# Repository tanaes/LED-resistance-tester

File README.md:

# LED-resistance-tester
Simple PCB for dialing in current limiting resistors for LEDs

## Inspiration

This project was broadly inspired by [this blog post on Sparkfun](https://news.sparkfun.com/5461), combined of course with the unceasing voice in my head to *design another stupid PCB*. 

## Usage

I set this board up to have four LED test 'stations' each on two parallel power rails. The idea is that you can easily match your brightness on, say, 5V and 24V. There's a jumper to link the two rails, too, in case you just want to test 8 different LEDs at the same voltage. There are big, ø5mm plated holes that are just the right size for grabbing with alligator clips for powering, as well as 5mm terminal blocks. 

LED current is set with DIP switches jumping over a ~ decadal series of common resistor values, with a minimum series resistance of 220Ω and a maximum of about 41kΩ (because DIP switches are fun).

Solder jumpers in parallel to the DIP switches offer an alternative (archival) mechanism, on the theory that one might want to dial this in for a particular vendor series and then toss it in a drawer for future reference. 

There are footprints for 0603 and 0805 SMT plus THT LEDs per channel, as well as big test pads for double-checking resistance values. 

Big white silkscreen areas are present on the front and back, in principle as a place to write down what the heck you have soldered onto the board for when you come across it in that drawer a year from now.

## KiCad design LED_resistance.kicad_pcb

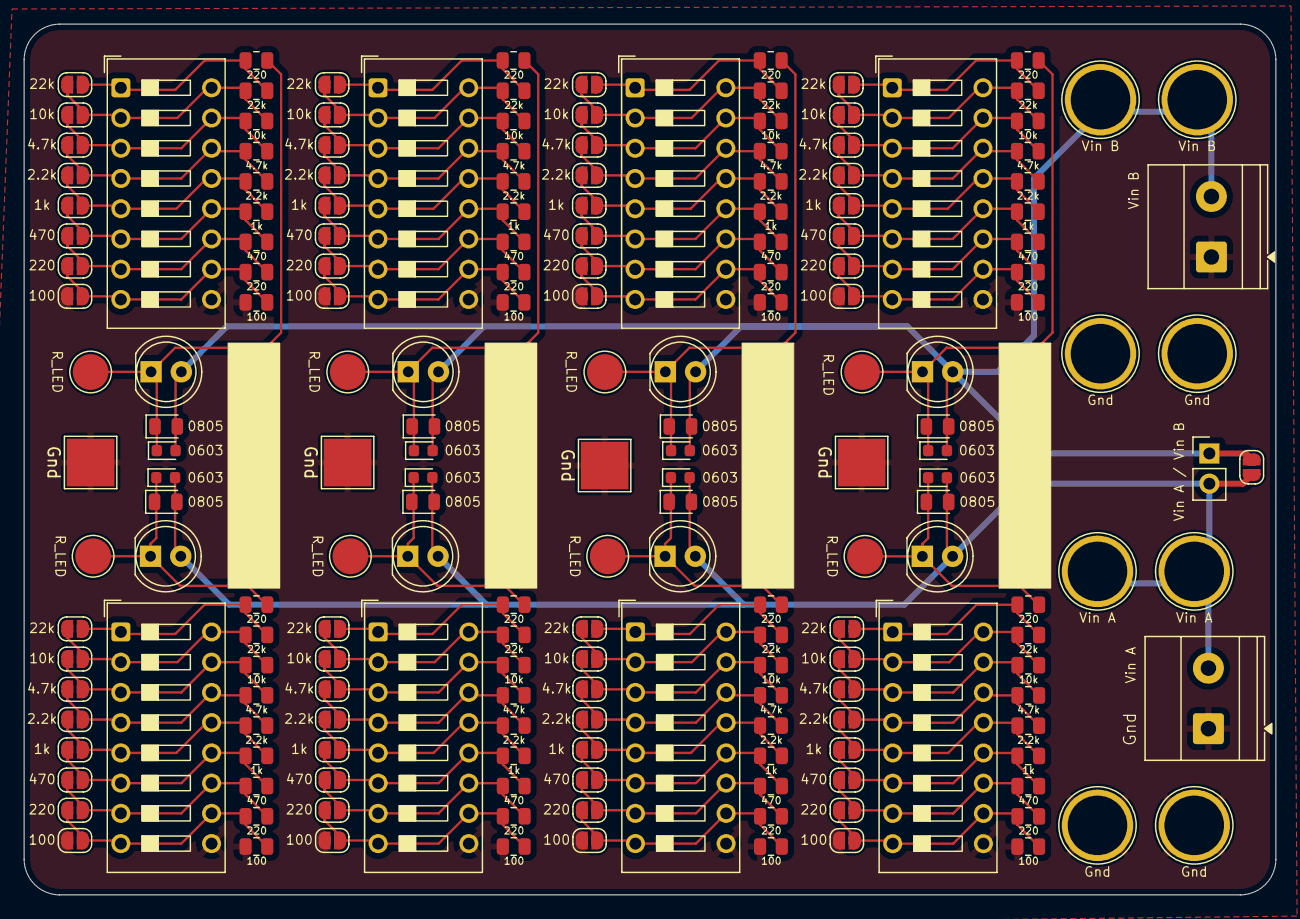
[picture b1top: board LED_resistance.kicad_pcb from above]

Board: 2 copper layers, 105.2 x 73.2 mm, 192 parts (0 on the bottom side), 75 nets.

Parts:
D1, D4, D7, D10, D13, D16, D19, D22: THT; LED_D5.0mm
D2, D5, D8, D11, D14, D17, D20, D23: 0805; LED_0805_2012Metric
D3, D6, D9, D12, D15, D18, D21, D24: 0603; LED_0603_1608Metric
J1: Vin A; TerminalBlock_Phoenix_MKDS-1,5-2-5.08_1x02_P5.08mm_Horizont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
J2: Vin B; TerminalBlock_Phoenix_MKDS-1,5-2-5.08_1x02_P5.08mm_Horizont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
JP1, JP9, JP17, JP25, JP33, JP41, JP49, JP57: 22k; SolderJumper-2_P1.3mm_Open_RoundedPad1.0x1.5mm
JP2, JP10, JP18, JP26, JP34, JP42, JP50, JP58: 10k; SolderJumper-2_P1.3mm_Open_RoundedPad1.0x1.5mm
JP3, JP11, JP19, JP27, JP35, JP43, JP51, JP59: 4.7k; SolderJumper-2_P1.3mm_Open_RoundedPad1.0x1.5mm
JP4, JP12, JP20, JP28, JP36, JP44, JP52, JP60: 2.2k; SolderJumper-2_P1.3mm_Open_RoundedPad1.0x1.5mm
JP5, JP13, JP21, JP29, JP37, JP45, JP53, JP61: 1k; SolderJumper-2_P1.3mm_Open_RoundedPad1.0x1.5mm
JP6, JP14, JP22, JP30, JP38, JP46, JP54, JP62: 470; SolderJumper-2_P1.3mm_Open_RoundedPad1.0x1.5mm
JP7, JP15, JP23, JP31, JP39, JP47, JP55, JP63: 220; SolderJumper-2_P1.3mm_Open_RoundedPad1.0x1.5mm
JP8, JP16, JP24, JP32, JP40, JP48, JP56, JP64: 100; SolderJumper-2_P1.3mm_Open_RoundedPad1.0x1.5mm
JP65: SolderJumper_2_Open; SolderJumper-2_P1.3mm_Open_RoundedPad1.0x1.5mm
JP66: Vin A / Vin B; PinHeader_1x02_P2.54mm_Vertical
R1, R8, R10, R17, R19, R26, R28, R35, R37, R44, R46, R53, R55, R62, R64, R71: 220; R_0805_2012Metric
R2, R11, R20, R29, R38, R47, R56, R65: 22k; R_0805_2012Metric
R3, R12, R21, R30, R39, R48, R57, R66: 10k; R_0805_2012Metric
R4, R13, R22, R31, R40, R49, R58, R67: 4.7k; R_0805_2012Metric
R5, R14, R23, R32, R41, R50, R59, R68: 2.2k; R_0805_2012Metric
R6, R15, R24, R33, R42, R51, R60, R69: 1k; R_0805_2012Metric
R7, R16, R25, R34, R43, R52, R61, R70: 470; R_0805_2012Metric
R9, R18, R27, R36, R45, R54, R63, R72: 100; R_0805_2012Metric
SW1, SW2, SW3, SW4, SW5, SW6, SW7, SW8: SW_DIP_x08; SW_DIP_SPSTx08_Slide_9.78x22.5mm_W7.62mm_P2.54mm
TP1, TP3: Vin A; TestPoint_Plated_Hole_D5.0mm
TP2, TP4, TP10, TP12: Gnd; TestPoint_Plated_Hole_D5.0mm
TP5, TP6, TP7, TP8, TP13, TP14, TP15, TP16: R_LED; TestPoint_Pad_D3.0mm
TP9, TP11: Vin B; TestPoint_Plated_Hole_D5.0mm
TP17, TP18, TP19, TP20: Gnd; TestPoint_Pad_4.0x4.0mm

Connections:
/led_subset2/Vin: D13.2 (A), D14.2 (A), D15.2 (A), D16.2 (A), D17.2 (A), D18.2 (A), D19.2 (A), D20.2 (A), D21.2 (A), D22.2 (A), D23.2 (A), D24.2 (A), J2.2, JP65.1 (A), JP66.1 (A), TP9.1, TP11.1
/led_subset/Vin: D1.2 (A), D2.2 (A), D3.2 (A), D4.2 (A), D5.2 (A), D6.2 (A), D7.2 (A), D8.2 (A), D9.2 (A), D10.2 (A), D11.2 (A), D12.2 (A), J1.2, JP65.2 (B), JP66.2 (B), TP1.1, TP3.1
GND: J1.1, J2.1, JP8.2 (B), JP16.2 (B), JP24.2 (B), JP32.2 (B), JP40.2 (B), JP48.2 (B), JP56.2 (B), JP64.2 (B), R9.2, R18.2, R27.2, R36.2, R45.2, R54.2, R63.2, R72.2, SW1.9, SW2.9, SW3.9, SW4.9, SW5.9, SW6.9, SW7.9, SW8.9, TP2.1, TP4.1, TP10.1, TP12.1, TP17.1, TP18.1, TP19.1, TP20.1
unnamed: D1.1 (K), D2.1 (K), D3.1 (K), R1.1, TP5.1
unnamed: D4.1 (K), D5.1 (K), D6.1 (K), R10.1, TP6.1
unnamed: D7.1 (K), D8.1 (K), D9.1 (K), R19.1, TP7.1
unnamed: D10.1 (K), D11.1 (K), D12.1 (K), R28.1, TP8.1
unnamed: D13.1 (K), D14.1 (K), D15.1 (K), R37.1, TP13.1
unnamed: D16.1 (K), D17.1 (K), D18.1 (K), R46.1, TP14.1
unnamed: D19.1 (K), D20.1 (K), D21.1 (K), R55.1, TP15.1
unnamed: D22.1 (K), D23.1 (K), D24.1 (K), R64.1, TP16.1
unnamed: JP1.1 (A), R1.2, R2.1, SW1.1
unnamed: JP1.2 (B), JP2.1 (A), R2.2, R3.1, SW1.2, SW1.16
unnamed: JP2.2 (B), JP3.1 (A), R3.2, R4.1, SW1.3, SW1.15
unnamed: JP3.2 (B), JP4.1 (A), R4.2, R5.1, SW1.4, SW1.14
unnamed: JP4.2 (B), JP5.1 (A), R5.2, R6.1, SW1.5, SW1.13
unnamed: JP5.2 (B), JP6.1 (A), R6.2, R7.1, SW1.6, SW1.12
unnamed: JP6.2 (B), JP7.1 (A), R7.2, R8.1, SW1.7, SW1.11
unnamed: JP7.2 (B), JP8.1 (A), R8.2, R9.1, SW1.8, SW1.10
unnamed: JP9.1 (A), R10.2, R11.1, SW2.1
unnamed: JP9.2 (B), JP10.1 (A), R11.2, R12.1, SW2.2, SW2.16
unnamed: JP10.2 (B), JP11.1 (A), R12.2, R13.1, SW2.3, SW2.15
unnamed: JP11.2 (B), JP12.1 (A), R13.2, R14.1, SW2.4, SW2.14
unnamed: JP12.2 (B), JP13.1 (A), R14.2, R15.1, SW2.5, SW2.13
unnamed: JP13.2 (B), JP14.1 (A), R15.2, R16.1, SW2.6, SW2.12
unnamed: JP14.2 (B), JP15.1 (A), R16.2, R17.1, SW2.7, SW2.11
unnamed: JP15.2 (B), JP16.1 (A), R17.2, R18.1, SW2.8, SW2.10
unnamed: JP17.1 (A), R19.2, R20.1, SW3.1
unnamed: JP17.2 (B), JP18.1 (A), R20.2, R21.1, SW3.2, SW3.16
unnamed: JP18.2 (B), JP19.1 (A), R21.2, R22.1, SW3.3, SW3.15
unnamed: JP19.2 (B), JP20.1 (A), R22.2, R23.1, SW3.4, SW3.14
unnamed: JP20.2 (B), JP21.1 (A), R23.2, R24.1, SW3.5, SW3.13
unnamed: JP21.2 (B), JP22.1 (A), R24.2, R25.1, SW3.6, SW3.12
unnamed: JP22.2 (B), JP23.1 (A), R25.2, R26.1, SW3.7, SW3.11
unnamed: JP23.2 (B), JP24.1 (A), R26.2, R27.1, SW3.8, SW3.10
unnamed: JP25.1 (A), R28.2, R29.1, SW4.1
unnamed: JP25.2 (B), JP26.1 (A), R29.2, R30.1, SW4.2, SW4.16
unnamed: JP26.2 (B), JP27.1 (A), R30.2, R31.1, SW4.3, SW4.15
unnamed: JP27.2 (B), JP28.1 (A), R31.2, R32.1, SW4.4, SW4.14
unnamed: JP28.2 (B), JP29.1 (A), R32.2, R33.1, SW4.5, SW4.13
unnamed: JP29.2 (B), JP30.1 (A), R33.2, R34.1, SW4.6, SW4.12
unnamed: JP30.2 (B), JP31.1 (A), R34.2, R35.1, SW4.7, SW4.11
unnamed: JP31.2 (B), JP32.1 (A), R35.2, R36.1, SW4.8, SW4.10
unnamed: JP33.1 (A), R37.2, R38.1, SW5.1
unnamed: JP33.2 (B), JP34.1 (A), R38.2, R39.1, SW5.2, SW5.16
unnamed: JP34.2 (B), JP35.1 (A), R39.2, R40.1, SW5.3, SW5.15
unnamed: JP35.2 (B), JP36.1 (A), R40.2, R41.1, SW5.4, SW5.14
unnamed: JP36.2 (B), JP37.1 (A), R41.2, R42.1, SW5.5, SW5.13
unnamed: JP37.2 (B), JP38.1 (A), R42.2, R43.1, SW5.6, SW5.12
unnamed: JP38.2 (B), JP39.1 (A), R43.2, R44.1, SW5.7, SW5.11
unnamed: JP39.2 (B), JP40.1 (A), R44.2, R45.1, SW5.8, SW5.10
unnamed: JP41.1 (A), R46.2, R47.1, SW6.1
unnamed: JP41.2 (B), JP42.1 (A), R47.2, R48.1, SW6.2, SW6.16
unnamed: JP42.2 (B), JP43.1 (A), R48.2, R49.1, SW6.3, SW6.15
unnamed: JP43.2 (B), JP44.1 (A), R49.2, R50.1, SW6.4, SW6.14
unnamed: JP44.2 (B), JP45.1 (A), R50.2, R51.1, SW6.5, SW6.13
unnamed: JP45.2 (B), JP46.1 (A), R51.2, R52.1, SW6.6, SW6.12
unnamed: JP46.2 (B), JP47.1 (A), R52.2, R53.1, SW6.7, SW6.11
unnamed: JP47.2 (B), JP48.1 (A), R53.2, R54.1, SW6.8, SW6.10
unnamed: JP49.1 (A), R55.2, R56.1, SW7.1
unnamed: JP49.2 (B), JP50.1 (A), R56.2, R57.1, SW7.2, SW7.16
unnamed: JP50.2 (B), JP51.1 (A), R57.2, R58.1, SW7.3, SW7.15
unnamed: JP51.2 (B), JP52.1 (A), R58.2, R59.1, SW7.4, SW7.14
unnamed: JP52.2 (B), JP53.1 (A), R59.2, R60.1, SW7.5, SW7.13
unnamed: JP53.2 (B), JP54.1 (A), R60.2, R61.1, SW7.6, SW7.12
unnamed: JP54.2 (B), JP55.1 (A), R61.2, R62.1, SW7.7, SW7.11
unnamed: JP55.2 (B), JP56.1 (A), R62.2, R63.1, SW7.8, SW7.10
unnamed: JP57.1 (A), R64.2, R65.1, SW8.1
unnamed: JP57.2 (B), JP58.1 (A), R65.2, R66.1, SW8.2, SW8.16
unnamed: JP58.2 (B), JP59.1 (A), R66.2, R67.1, SW8.3, SW8.15
unnamed: JP59.2 (B), JP60.1 (A), R67.2, R68.1, SW8.4, SW8.14
unnamed: JP60.2 (B), JP61.1 (A), R68.2, R69.1, SW8.5, SW8.13
unnamed: JP61.2 (B), JP62.1 (A), R69.2, R70.1, SW8.6, SW8.12
unnamed: JP62.2 (B), JP63.1 (A), R70.2, R71.1, SW8.7, SW8.11
unnamed: JP63.2 (B), JP64.1 (A), R71.2, R72.1, SW8.8, SW8.10

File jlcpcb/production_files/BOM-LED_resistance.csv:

Comment,Designator,Footprint,LCSC,Quantity
R_LED,TP14,TestPoint_Pad_D3.0mm,,1
R_LED,TP5,TestPoint_Pad_D3.0mm,,1
R_LED,TP6,TestPoint_Pad_D3.0mm,,1
Gnd,TP20,TestPoint_Pad_4.0x4.0mm,,1
Gnd,TP19,TestPoint_Pad_4.0x4.0mm,,1
Gnd,TP18,TestPoint_Pad_4.0x4.0mm,,1
Gnd,TP17,TestPoint_Pad_4.0x4.0mm,,1
THT,D19,LED_D5.0mm,,1
0805,D20,LED_0805_2012Metric,,1
0603,D21,LED_0603_1608Metric,,1
220,R55,R_0805_2012Metric,,1
22k,R56,R_0805_2012Metric,,1
10k,R57,R_0805_2012Metric,,1
4.7k,R58,R_0805_2012Metric,,1
2.2k,R59,R_0805_2012Metric,,1
1k,R60,R_0805_2012Metric,,1
470,R61,R_0805_2012Metric,,1
220,R62,R_0805_2012Metric,,1
100,R63,R_0805_2012Metric,,1
SW_DIP_x08,SW7,SW_DIP_SPSTx08_Slide_9.78x22.5mm_W7.62mm_P2.54mm,,1
R_LED,TP15,TestPoint_Pad_D3.0mm,,1
THT,D22,LED_D5.0mm,,1
0805,D23,LED_0805_2012Metric,,1
0603,D24,LED_0603_1608Metric,,1
220,R64,R_0805_2012Metric,,1
22k,R65,R_0805_2012Metric,,1
10k,R66,R_0805_2012Metric,,1
4.7k,R67,R_0805_2012Metric,,1
2.2k,R68,R_0805_2012Metric,,1
1k,R69,R_0805_2012Metric,,1
470,R70,R_0805_2012Metric,,1
220,R71,R_0805_2012Metric,,1
100,R72,R_0805_2012Metric,,1
SW_DIP_x08,SW8,SW_DIP_SPSTx08_Slide_9.78x22.5mm_W7.62mm_P2.54mm,,1
R_LED,TP16,TestPoint_Pad_D3.0mm,,1
THT,D13,LED_D5.0mm,,1
0805,D14,LED_0805_2012Metric,,1
0603,D15,LED_0603_1608Metric,,1
220,R37,R_0805_2012Metric,,1
22k,R38,R_0805_2012Metric,,1
10k,R39,R_0805_2012Metric,,1
4.7k,R40,R_0805_2012Metric,,1
2.2k,R41,R_0805_2012Metric,,1
1k,R42,R_0805_2012Metric,,1
470,R43,R_0805_2012Metric,,1
220,R44,R_0805_2012Metric,,1
100,R45,R_0805_2012Metric,,1
SW_DIP_x08,SW5,SW_DIP_SPSTx08_Slide_9.78x22.5mm_W7.62mm_P2.54mm,,1
R_LED,TP13,TestPoint_Pad_D3.0mm,,1
0603,D18,LED_0603_1608Metric,,1
THT,D16,LED_D5.0mm,,1
0805,D17,LED_0805_2012Metric,,1
THT,D1,LED_D5.0mm,,1
0603,D3,LED_0603_1608Metric,,1
0805,D2,LED_0805_2012Metric,,1
SW_DIP_x08,SW1,SW_DIP_SPSTx08_Slide_9.78x22.5mm_W7.62mm_P2.54mm,,1
220,R1,R_0805_2012Metric,,1
22k,R2,R_0805_2012Metric,,1
10k,R3,R_0805_2012Metric,,1
4.7k,R4,R_0805_2012Metric,,1
2.2k,R5,R_0805_2012Metric,,1
1k,R6,R_0805_2012Metric,,1
470,R7,R_0805_2012Metric,,1
220,R8,R_0805_2012Metric,,1
100,R9,R_0805_2012Metric,,1
0603,D6,LED_0603_1608Metric,,1
0805,D5,LED_0805_2012Metric,,1
220,R10,R_0805_2012Metric,,1
22k,R11,R_0805_2012Metric,,1
1k,R15,R_0805_2012Metric,,1
220,R17,R_0805_2012Metric,,1
2.2k,R14,R_0805_2012Metric,,1
SW_DIP_x08,SW2,SW_DIP_SPSTx08_Slide_9.78x22.5mm_W7.62mm_P2.54mm,,1
100,R18,R_0805_2012Metric,,1
10k,R12,R_0805_2012Metric,,1
470,R16,R_0805_2012Metric,,1
THT,D4,LED_D5.0mm,,1
4.7k,R13,R_0805_2012Metric,,1
Vin A,J1,"TerminalBlock_Phoenix_MKDS-1,5-2-5.08_1x02_P5.08mm_Horizontal",,1
Gnd,TP2,TestPoint_Plated_Hole_D5.0mm,,1
Vin A,TP1,TestPoint_Plated_Hole_D5.0mm,,1
Vin A,TP3,TestPoint_Plated_Hole_D5.0mm,,1
Gnd,TP4,TestPoint_Plated_Hole_D5.0mm,,1
22k,R47,R_0805_2012Metric,,1
SW_DIP_x08,SW6,SW_DIP_SPSTx08_Slide_9.78x22.5mm_W7.62mm_P2.54mm,,1
10k,R48,R_0805_2012Metric,,1
220,R53,R_0805_2012Metric,,1
470,R52,R_0805_2012Metric,,1
2.2k,R50,R_0805_2012Metric,,1
1k,R51,R_0805_2012Metric,,1
220,R46,R_0805_2012Metric,,1
100,R54,R_0805_2012Metric,,1
4.7k,R49,R_0805_2012Metric,,1
Gnd,TP12,TestPoint_Plated_Hole_D5.0mm,,1
Vin B,TP11,TestPoint_Plated_Hole_D5.0mm,,1
Gnd,TP10,TestPoint_Plated_Hole_D5.0mm,,1
Vin B,TP9,TestPoint_Plated_Hole_D5.0mm,,1
Vin A / Vin B,JP66,PinHeader_1x02_P2.54mm_Vertical,,1
Vin B,J2,"TerminalBlock_Phoenix_MKDS-1,5-2-5.08_1x02_P5.08mm_Horizontal",,1
THT,D10,LED_D5.0mm,,1
SW_DIP_x08,SW4,SW_DIP_SPSTx08_Slide_9.78x22.5mm_W7.62mm_P2.54mm,,1
220,R35,R_0805_2012Metric,,1
100,R36,R_0805_2012Metric,,1
10k,R30,R_0805_2012Metric,,1
R_LED,TP8,TestPoint_Pad_D3.0mm,,1
0603,D12,LED_0603_1608Metric,,1
22k,R29,R_0805_2012Metric,,1
0805,D11,LED_0805_2012Metric,,1
1k,R33,R_0805_2012Metric,,1
220,R28,R_0805_2012Metric,,1
4.7k,R31,R_0805_2012Metric,,1
470,R34,R_0805_2012Metric,,1
2.2k,R32,R_0805_2012Metric,,1
4.7k,R22,R_0805_2012Metric,,1
220,R19,R_0805_2012Metric,,1
470,R25,R_0805_2012Metric,,1
100,R27,R_0805_2012Metric,,1
10k,R21,R_0805_2012Metric,,1
SW_DIP_x08,SW3,SW_DIP_SPSTx08_Slide_9.78x22.5mm_W7.62mm_P2.54mm,,1
1k,R24,R_0805_2012Metric,,1
0805,D8,LED_0805_2012Metric,,1
THT,D7,LED_D5.0mm,,1
0603,D9,LED_0603_1608Metric,,1
220,R26,R_0805_2012Metric,,1
R_LED,TP7,TestPoint_Pad_D3.0mm,,1
2.2k,R23,R_0805_2012Metric,,1
22k,R20,R_0805_2012Metric,,1

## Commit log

2025-11-17 added CERN OHL
2025-11-17 wrote some stuff in README
2025-11-17 added images
